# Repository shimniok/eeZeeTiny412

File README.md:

# eeZeeTiny412
Breakout/target board for ATtiny212/412

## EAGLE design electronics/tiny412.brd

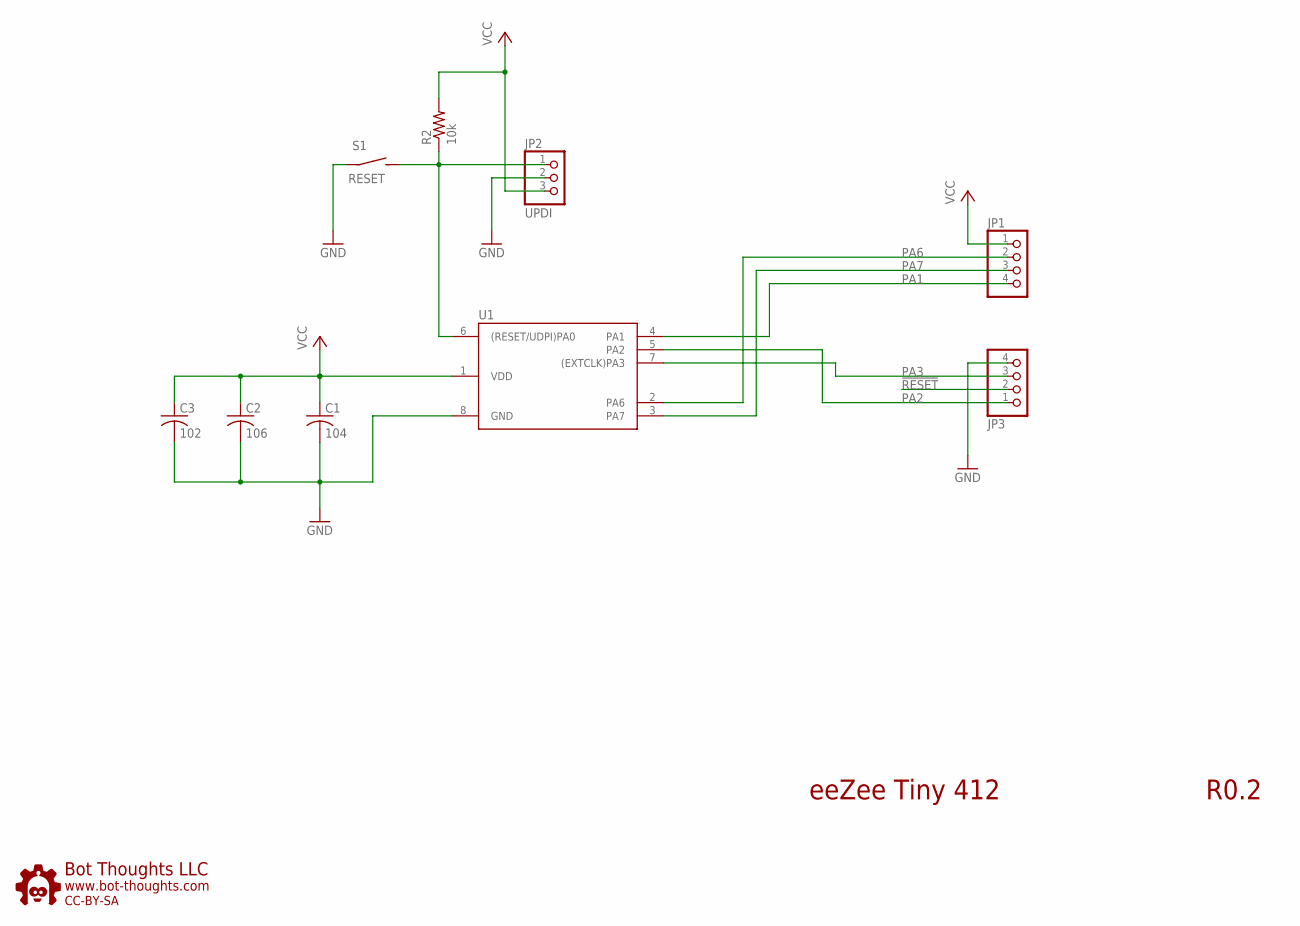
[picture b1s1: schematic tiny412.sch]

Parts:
C1: 104; C0603; PARTNO 0603YC104KAT2A
C2: 106; 0603; PARTNO MCTT21X106M6R3CT
C3: 102; C0603; PARTNO 0603YC104KAT2A
JP1, JP3: PINHD-1X04_2.54-S; 1X04-S
JP2: UPDI; 1X03-S
R2: 10k; R0603; PARTNO ERJ-3GEYJ103V
S1: RESET; 3X4X2TACT
U1: ATTINY212/412; SOIC8N
U$1: BTLOGO-LOGO-MD; BTLOGOM

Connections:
!RESET: JP2.1, JP3.2, R2.1, S1.P$2 (S), U1.6 ((RESET/UDPI)PA0)
GND: C1.2, C2.2 (-), C3.2, JP2.2, JP3.4, S1.P$1, U1.8 (GND)
PA1: JP1.4, U1.4 (PA1)
PA2: JP3.1, U1.5 (PA2)
PA3: JP3.3, U1.7 ((EXTCLK)PA3)
PA6: JP1.2, U1.2 (PA6)
PA7: JP1.3, U1.3 (PA7)
VCC: C1.1, C2.1 (+), C3.1, JP1.1, JP2.3, R2.2, U1.1 (VDD)

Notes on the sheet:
eeZee Tiny 412
R0.2

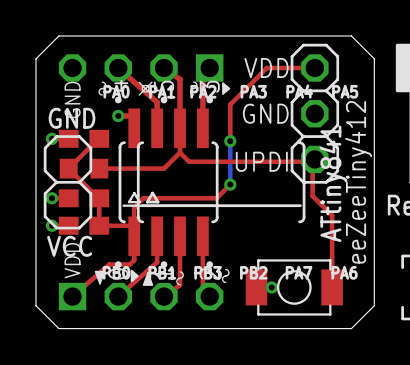
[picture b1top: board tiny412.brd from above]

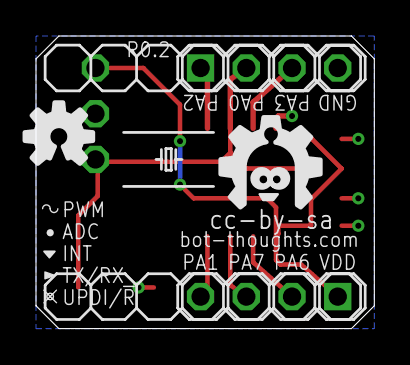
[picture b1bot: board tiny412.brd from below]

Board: 2 copper layers, 18.8 x 16.3 mm, 26 parts (4 on the bottom side), 8 nets.

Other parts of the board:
U$2, U$3, U$6, U$7: ARDUINO_PWM
U$4, U$5: ARDUINO_ASYNC
U$8, U$9: ARDUINO_TXD_RXD
U$10: ARDUINO_LEGEND
U$11: ARDUINO_UDPI_RESET
U$12, U$13, U$14, U$15, U$16, U$17: ARDUINO_ANALOG

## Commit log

2022-05-04 initial schematic & board
2022-05-04 add documentation stub
2022-05-04 added zip
2022-05-21 Updated silk symbols, enlarged; fixed reset ckt, added HF filter cap
2023-08-27 added text to readme
2023-08-27 remove reset, updated pin desc, added doc url

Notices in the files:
electronics/tiny412.brd:
cc-by-sa
